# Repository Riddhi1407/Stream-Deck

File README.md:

# Stream-Deck
***

This is a Multifunction Programmable deck with 8 keys programmable graphical keypad, a 4.3 inch multifunctional tft lcd screen with touch and 2 programmable rotary knobs with switches. It has user customizable haptic feedback, that can be customized on the deviceitself. The deck has Bluetooth and Wi-Fi connectivity options and can be used wirelessly tocontrol connected peripherals. It also has a Lithium-Polymer battery with Type-C charging forwireless use that provides a battery life of 10 hour.

**Features:**
-8 keys Programmable Graphical Keypad
-4.3 inch TFT LCD Multifunction Screen with Capacitive Touch
-2 Rotary knobs with switches
-Haptic Feedback
-Bluetooth 5.3 and Wi-Fi
-Type-C Charging
-10 Hour Battery Life

### Keypad  
The 8 key graphical keypad can show the graphics on the keys. Keys of the keypad becustomized using the onboard tft lcd to show diferent graphics. The functions of the keyscan also be set or changed using the deck itself or other device. Keypad customizations canbe saved as modes and can be reused as presets.

### Display
The 4.3 inch tft lcd display with capacitive touch is used for controlling the functions of thedeck and also for controlling the connected peripherals. The screen can also be used astrackpad by turning off the backlight and/or numpad by selecting these options on the deckitself.

### Knobs 
Similar to the keypad, the rotary knobs and their switches can also be customized using theonboard lcd display. The primary function to control the lcd interface, however it can bechanged for doing any task.

### Haptics
The deck has haptic feedback feature for key presses, touch interactions with the displayand for the rotary knobs and their switches. The haptic feedback function can be customizedfor key presses, touch interactions and rotary knobs or it can also be completely turned ofusing the screen.

### Wireless
The deck has Bluetooth 5.3 and Wi-Fi wireless connectivity options to control the connectedperipherals and the deck using other device. The deck van also br connected through USBType-C for controlling the connected peripherals or device and it can also be used to controlor program the deck.

### Power
The deck has a 10000 mAh Lithium-Polymer battery that can power the device for 10 hour inwireless mode and not connected to power. It can be charged by USB Type-C. The deck canalso be powered by USB Type-C.

### Schematic
**Main Schematic**

**Keypad Top Layer Schematic**

**Keypad Bottom Layer Schematic**

### PCB Layout  

### PCB 3D CAD
**PCB Front**

**PCB Back**

### CASE 3D CAD

**Assembly**

**Assembly Top**

**Case Top**

**Case Bottom**

**Display 1** 

**Display 2**

**Keycap** 

**Rubber Membrane**

**Spacer**

**Knob**

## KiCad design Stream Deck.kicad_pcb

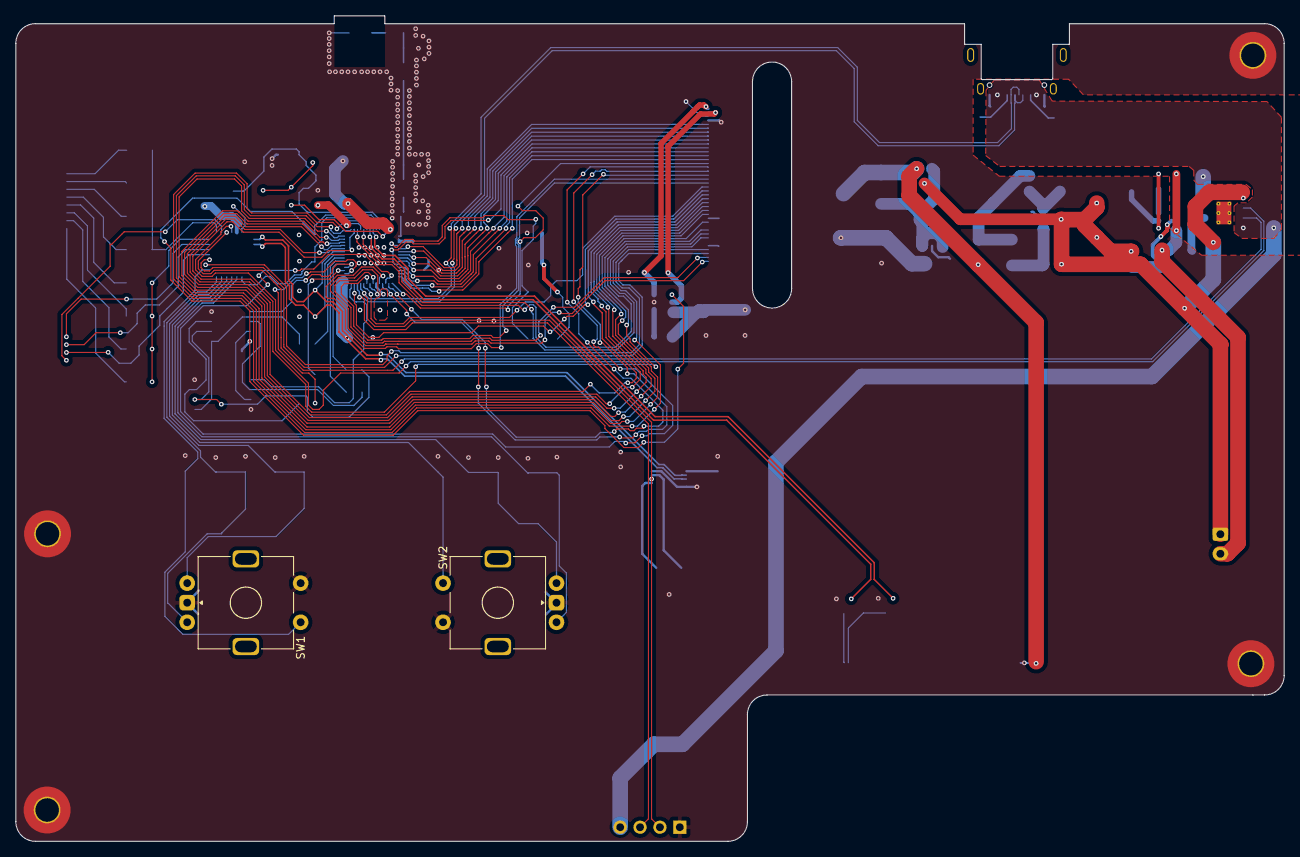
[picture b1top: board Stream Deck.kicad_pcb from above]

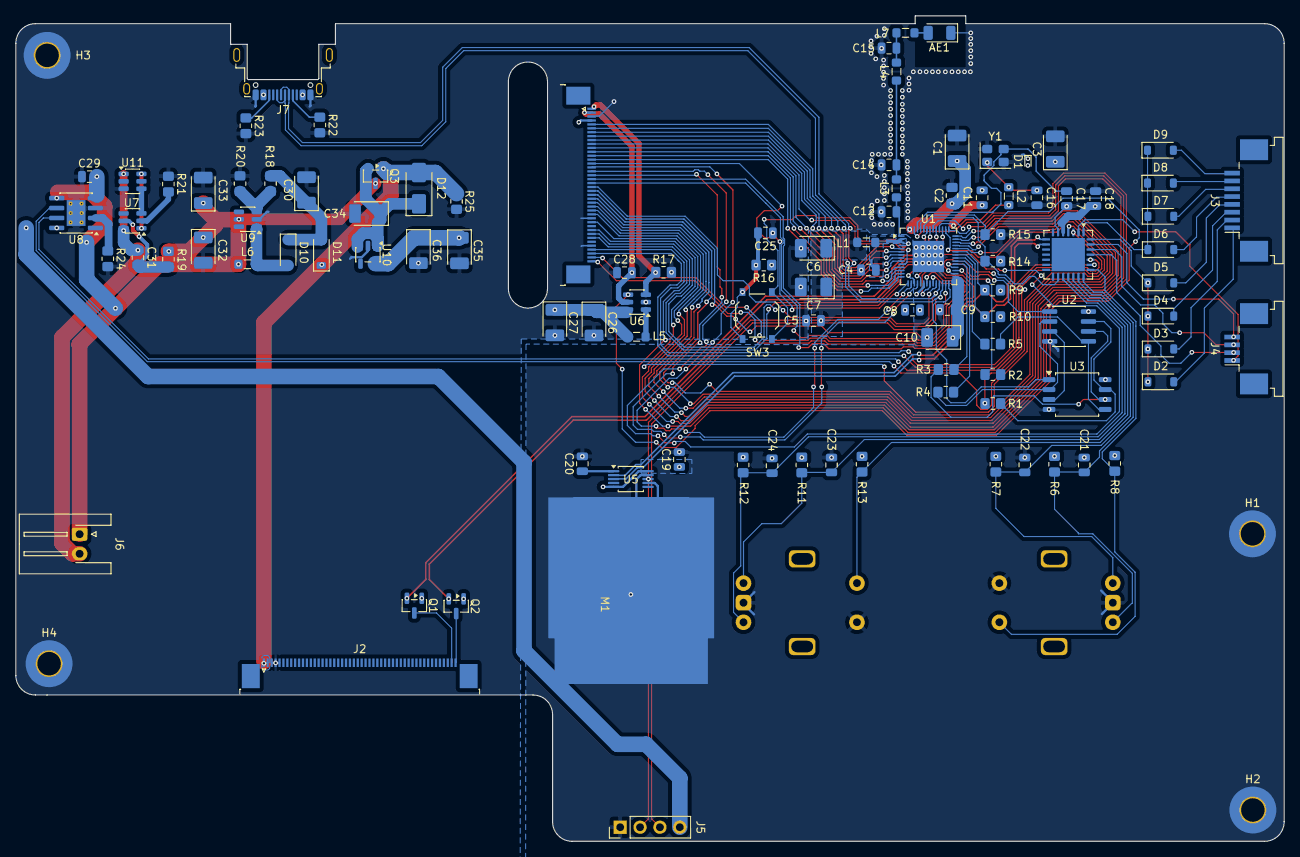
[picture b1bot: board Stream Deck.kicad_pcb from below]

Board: 4 copper layers, 162.1 x 105.5 mm, 110 parts (108 on the bottom side), 109 nets.

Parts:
AE1: Antenna_Chip; Johanson_2450AT18x100_2400-2500Mhz
C1, C3, C6, C7, C32, C34, C35: 10uF; CP_EIA-3528-21_Kemet-B_HandSolder
C2: 10nF; C_0805_2012Metric_Pad1.18x1.45mm_HandSolder
C4, C5, C8, C9, C11, C18, C19, C20, C21, C22, C23, C24, C25: 0.1uF; C_0805_2012Metric
C10, C26, C27, C36: 1uF; CP_EIA-3528-21_Kemet-B_HandSolder
C12, C14, C15: C; C_0805_2012Metric
C16, C17: 24pF; C_0805_2012Metric
C28: 220nF; C_0805_2012Metric
C29, C31: 100nF; C_0805_2012Metric
C30, C33: 22uF; CP_EIA-3528-21_Kemet-B_HandSolder
D1: ESD9B3.3ST5G; D_SOD-923
D2, D3, D4, D5, D6, D7, D8, D9: D; D_SOD-123
D10, D11: 1N5822; D_SOD-123
D12: SS34; D_SMA
H1, H2, H3, H4: MountingHole_Pad; MountingHole_3mm_Pad_TopBottom
J1: Conn_01x40_MountingPin; TE_4-1734839-0_1x40-1MP_P0.5mm_Horizontal
J2: Conn_01x50_MountingPin; TE_5-1734839-0_1x50-1MP_P0.5mm_Horizontal
J3: Conn_01x08_MountingPin; TE_84952-8_1x08-1MP_P1.0mm_Horizontal
J4: Conn_01x04_MountingPin; TE_84952-4_1x04-1MP_P1.0mm_Horizontal
J5: Conn_01x04_Pin; PinHeader_1x04_P2.54mm_Vertical
J6: Conn_01x02_Pin; JST_XH_S2B-XH-A-1_1x02_P2.50mm_Horizontal
J7: USB_C_Receptacle_USB2.0_16P; USB_C_Receptacle_Amphenol_12401948E412A
L1: 2nH; L_0805_2012Metric_Pad1.05x1.20mm_HandSolder
L2: 24nH; L_0805_2012Metric_Pad1.05x1.20mm_HandSolder
L3, L4, L7: L; L_0805_2012Metric_Pad1.05x1.20mm_HandSolder
L5, L6: 22uH; L_0805_2012Metric_Pad1.05x1.20mm_HandSolder
M1: Motor_DC; PUI HD-EMB1104 Motor
Q1, Q2: BSS138; SOT-23
Q3: AO3401A; SOT-23
R1, R2, R3, R4, R5: 0; R_0805_2012Metric_Pad1.20x1.40mm_HandSolder
R6, R7, R8, R11, R12, R13, R14, R15, R16: 10K; R_0805_2012Metric_Pad1.20x1.40mm_HandSolder
R9, R10: 2.2K; R_0805_2012Metric_Pad1.20x1.40mm_HandSolder
R17: 2; R_0805_2012Metric_Pad1.20x1.40mm_HandSolder
R18: 7.5k; R_0805_2012Metric_Pad1.20x1.40mm_HandSolder
R19: 100; R_0805_2012Metric_Pad1.20x1.40mm_HandSolder
R20: 1k; R_0805_2012Metric_Pad1.20x1.40mm_HandSolder
R21: 1K; R_0805_2012Metric_Pad1.20x1.40mm_HandSolder
R22, R23: 5.1K; R_0805_2012Metric_Pad1.20x1.40mm_HandSolder
R24: 1.2k; R_0805_2012Metric_Pad1.20x1.40mm_HandSolder
R25: 100K; R_0805_2012Metric_Pad1.20x1.40mm_HandSolder
SW1, SW2: RotaryEncoder_Switch; ROT_Alps_EC11E-Switch
SW3: SW_Push; SW_Push_1P1T_XKB_TS-1187A
U1: ESP32-S3; QFN-56-1EP_7x7mm_P0.4mm_EP4x4mm
U2: ESP-PSRAM64H; SOIC-8_3.9x4.9mm_P1.27mm
U3: W25Q16JVSS; SOIC-8_5.3x5.3mm_P1.27mm
U4: MCP23017_ML; QFN-28-1EP_6x6mm_P0.65mm_EP4.25x4.25mm
U5: DRV2605LDGS; VSSOP-10_3x3mm_P0.5mm
U6: AP3019AKTTR; TSOT-23-6
U7: DW01A; SOT-23-6
U8: TP4056-42-ESOP8; SOIC-8-1EP_3.9x4.9mm_P1.27mm_EP2.41x3.3mm_ThermalVias
U9: SDB628; SOT-23-6
U10: AP2112K-3.3; SOT-23-5
U11: FS8205; SOT-23-6
Y1: YSX321SL 40MHz; Oscillator_SMD_Abracon_ASE-4Pin_3.2x2.5mm

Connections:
+3V3: C1.1, C2.1, C3.1, C5.1, C6.1, C7.1, C8.1, C9.1, C10.1, C11.1, C18.1, C19.1, C26.1, C27.1, C35.1, C36.1, D1.2 (A2), J1.4, L1.2, L5.1, Q1.1 (G), Q2.1 (G), R6.1, R7.1, R8.1, R9.1, R10.1, R11.1, R12.1, R13.1, R14.1, R16.1, U1.20 (VDD3P3_RTC), U1.29 (VDD_SPI), U1.46 (VDD3P3_CPU), U1.55 (VDDA), U1.56 (VDDA), U2.8 (VCC), U3.8 (VCC), U4.5 (VDD), U5.5 (EN), U5.10 (VDD), U6.6 (V_{IN}), U10.5 (VOUT)
+5V: D11.1 (K), D12.2 (A), J2.1, J2.2, Q3.1 (G), R25.1
/A: C28.1, J1.2, U6.5 (V_{OUT})
/B0: J1.21, U1.24 (GPIO18)
/B1: J1.22, U1.27 (GPIO21)
/B2: J1.23, U1.38 (GPIO33)
/B3: J1.24, U1.39 (GPIO34)
/B4: J1.25, U1.40 (GPIO35)
/B5: J1.26, U1.41 (GPIO36)
/B6: J1.27, U1.42 (GPIO37)
/B7: J1.28, U1.43 (GPIO38)
/B+: C32.1, C33.1, J6.1, L6.1, Q3.3 (D), R19.2, U8.5 (BAT), U9.5 (IN)
/B-: C31.2, J6.2, U7.6 (VSS), U11.1 (S1)
/CHRG: U4.3 (GPB6), U8.7 (~CHRG)
/CLK: J1.30, U1.44 (MTCK)
/COL0: J4.1, U4.2 (GPB5)
/COL1: J4.2, U4.25 (GPB0)
/COL2: J4.3, U4.26 (GPB1)
/COL3: J4.4, U4.27 (GPB2)
/CS0: U1.32 (SPICS0), U2.1 (~CE)
/CS1: U1.28 (SPICS1), U3.1 (~CS)
/CS2: J1.38, U4.24 (GPA7)
/CTRL: R15.1, U1.52 (GPIO46), U6.4 (CTRL)
/D+: J5.2, J7.A6 (D+), J7.B6 (D+), U1.26 (GPIO20/USB_D+)
/D-: J5.3, J7.A7 (D-), J7.B7 (D-), U1.25 (GPIO19/USB_D-)
/DE: J1.34, U1.48 (MTMS)
/EC1A: C22.1, R7.2, SW1.A, U4.20 (GPA3)
/EC1B: C21.1, R6.2, SW1.B, U4.21 (GPA4)
/EC1S: R8.2, SW1.S1, U4.22 (GPA5)
/EC2A: C24.1, R12.2, SW2.A, U4.17 (GPA0)
/EC2B: C23.1, R11.2, SW2.B, U4.18 (GPA1)
/EC2S: R13.2, SW2.S1, U4.19 (GPA2)
/G0: J1.13, U1.13 (GPIO8)
/G1: J1.14, U1.14 (GPIO9)
/G2: J1.15, U1.15 (GPIO10)
/G3: J1.16, U1.16 (GPIO11)
/G4: J1.17, U1.17 (GPIO12)
/G5: J1.18, U1.18 (GPIO13)
/G6: J1.19, U1.19 (GPIO14)
/G7: J1.20, U1.23 (GPIO17)
/HS: J1.32, U1.45 (MTDO)
/INTA: R14.2, U1.51 (GPIO45), U4.16 (INTA)
/K: J1.1, R17.1, U6.3 (FB)
/OUT+: M1.+, U5.7 (OUT+)
/OUT-: M1.-, U5.9 (OUT-)
/R0: J1.5, U1.5 (GPIO0)
/R1: J1.6, U1.6 (GPIO1)
/R2: J1.7, U1.7 (GPIO2)
/R3: J1.8, U1.8 (GPIO3)
/R4: J1.9, U1.9 (GPIO4)
/R5: J1.10, U1.10 (GPIO5)
/R6: J1.11, U1.11 (GPIO6)
/R7: J1.12, U1.12 (GPIO7)
/ROW0: D2.1 (K), D3.1 (K), D4.1 (K), D5.1 (K), U4.28 (GPB3)
/ROW1: D6.1 (K), D7.1 (K), D8.1 (K), D9.1 (K), U4.1 (GPB4)
/RST: J1.37, U4.23 (GPA6)
/RXD: Q1.2 (S), U1.50 (U0RXD)
/SCL: R9.2, U1.37 (SPICLK_P), U4.8 (SCK), U5.2 (SCL)
/SCL0: J1.39, U1.21 (XTAL_32K_P)
/SCLK: R3.2, U2.6 (SCLK), U3.6 (CLK)
/SDA: R10.2, U1.36 (SPICLK_N), U4.9 (SDA), U5.3 (SDA)
/SDA0: J1.40, U1.22 (XTAL_32K_N)
/SI: R5.2, U2.5 (SI/SIO), U3.5 (DI/IO_{0})
/SIO2: U2.3 (SIO2), U3.3 (~WP/IO_{2})
/SIO3: R1.2, U2.7 (SIO3), U3.7 (~HOLD/~RESET/IO_{3})
/SO: R4.2, U2.2 (SO/SIO), U3.2 (DO/IO_{1})
/STDBY: U4.4 (GPB7), U8.6 (~STDBY)
/SW0: D2.2 (A), J3.1
/SW1: D3.2 (A), J3.2
/SW2: D4.2 (A), J3.3
/SW3: D5.2 (A), J3.4
/SW4: D6.2 (A), J3.5
/SW5: D7.2 (A), J3.6
/SW6: D8.2 (A), J3.7
/SW7: D9.2 (A), J3.8
/TXD: Q2.2 (S), U1.49 (U0TXD)
/VS: J1.33, U1.47 (MTDI)
GND: AE1.1 (FEED), C1.2, C2.2, C3.2, C4.2, C5.2, C6.2, C7.2, C8.2, C9.2, C10.2, C11.2, C12.1, C14.1, C15.2, C16.2, C17.2, C18.2, C19.2, C20.2, C21.2, C22.2, C23.2, C24.2, C25.2, C26.2, C27.2, C28.2, C29.2, C30.2, C32.2, C33.2, C34.2, C35.2, C36.2, D1.1 (A1), H1.1, H2.1, H3.1, H4.1, J1.3, J1.29, J1.36, J2.3, J2.4, J2.5, J5.4, J7.A1 (GND), J7.A12 (GND), J7.B1 (GND), J7.B12 (GND), M1.GND, R15.2, R17.2, R20.2, R21.1, R22.2, R23.2, R24.2, R25.2, SW1.C, SW1.S2, SW2.C, SW2.S2, U1.57 (GND), U2.4 (VSS), U3.4 (GND), U4.6 (VSS), U5.8 (GND), U6.2 (GND), U8.3 (GND), U8.9 (EPAD), U9.2 (GND), U10.2 (GND), U11.3 (S2), Y1.2 (GND), Y1.4 (GND)
unnamed: AE1.2 (PCB_Trace), L7.2
unnamed: C4.1, L1.1, U1.2 (VDD3P3), U1.3 (VDD3P3)
unnamed: C14.2, L3.2, L4.1
unnamed: C15.1, L4.2, L7.1
unnamed: C25.1, R16.2, SW3.2
unnamed: D10.2 (A), L6.2, U9.1 (SW)
unnamed: C30.1, D10.1 (K), D11.2 (A), R18.1
unnamed: C34.1, D12.1 (K), Q3.2 (S), U10.1 (VIN), U10.3 (EN)
unnamed: J2.49, Q1.3 (D)
unnamed: J2.50, Q2.3 (D)
unnamed: J7.A5 (CC1), R22.1
unnamed: J7.B5 (CC2), R23.1
unnamed: SW3.1, U1.4 (CHIP_PU)
unnamed: C12.2, L3.1, U1.1 (LNA_IN)
unnamed: R3.1, U1.33 (SPICLK)
unnamed: R5.1, U1.35 (SPID)
unnamed: R1.1, U1.30 (SPIHD)
unnamed: R4.1, U1.34 (SPIQ)
unnamed: R2.1, U1.31 (SPIWP)
unnamed: C17.1, U1.53 (XTAL_N), Y1.3 (XOUT)
unnamed: L2.2, U1.54 (XTAL_P)
unnamed: C20.1, U5.1 (REG)
unnamed: L5.2, U6.1 (SW)
unnamed: R21.2, U7.2 (CSI)
unnamed: C31.1, R19.1, U7.5 (VDD)
unnamed: R24.1, U8.2 (PROG)
unnamed: R18.2, R20.1, U9.3 (FB)
unnamed: U7.1 (OD), U11.6 (G1)
unnamed: U7.3 (OC), U11.4 (G2)
unnamed: C16.1, L2.1, Y1.1 (XIN)
VBUS: C29.1, J5.1, J7.A4 (VBUS), J7.A9 (VBUS), J7.B4 (VBUS), J7.B9 (VBUS), U8.4 (V_{CC}), U8.8 (CE)
